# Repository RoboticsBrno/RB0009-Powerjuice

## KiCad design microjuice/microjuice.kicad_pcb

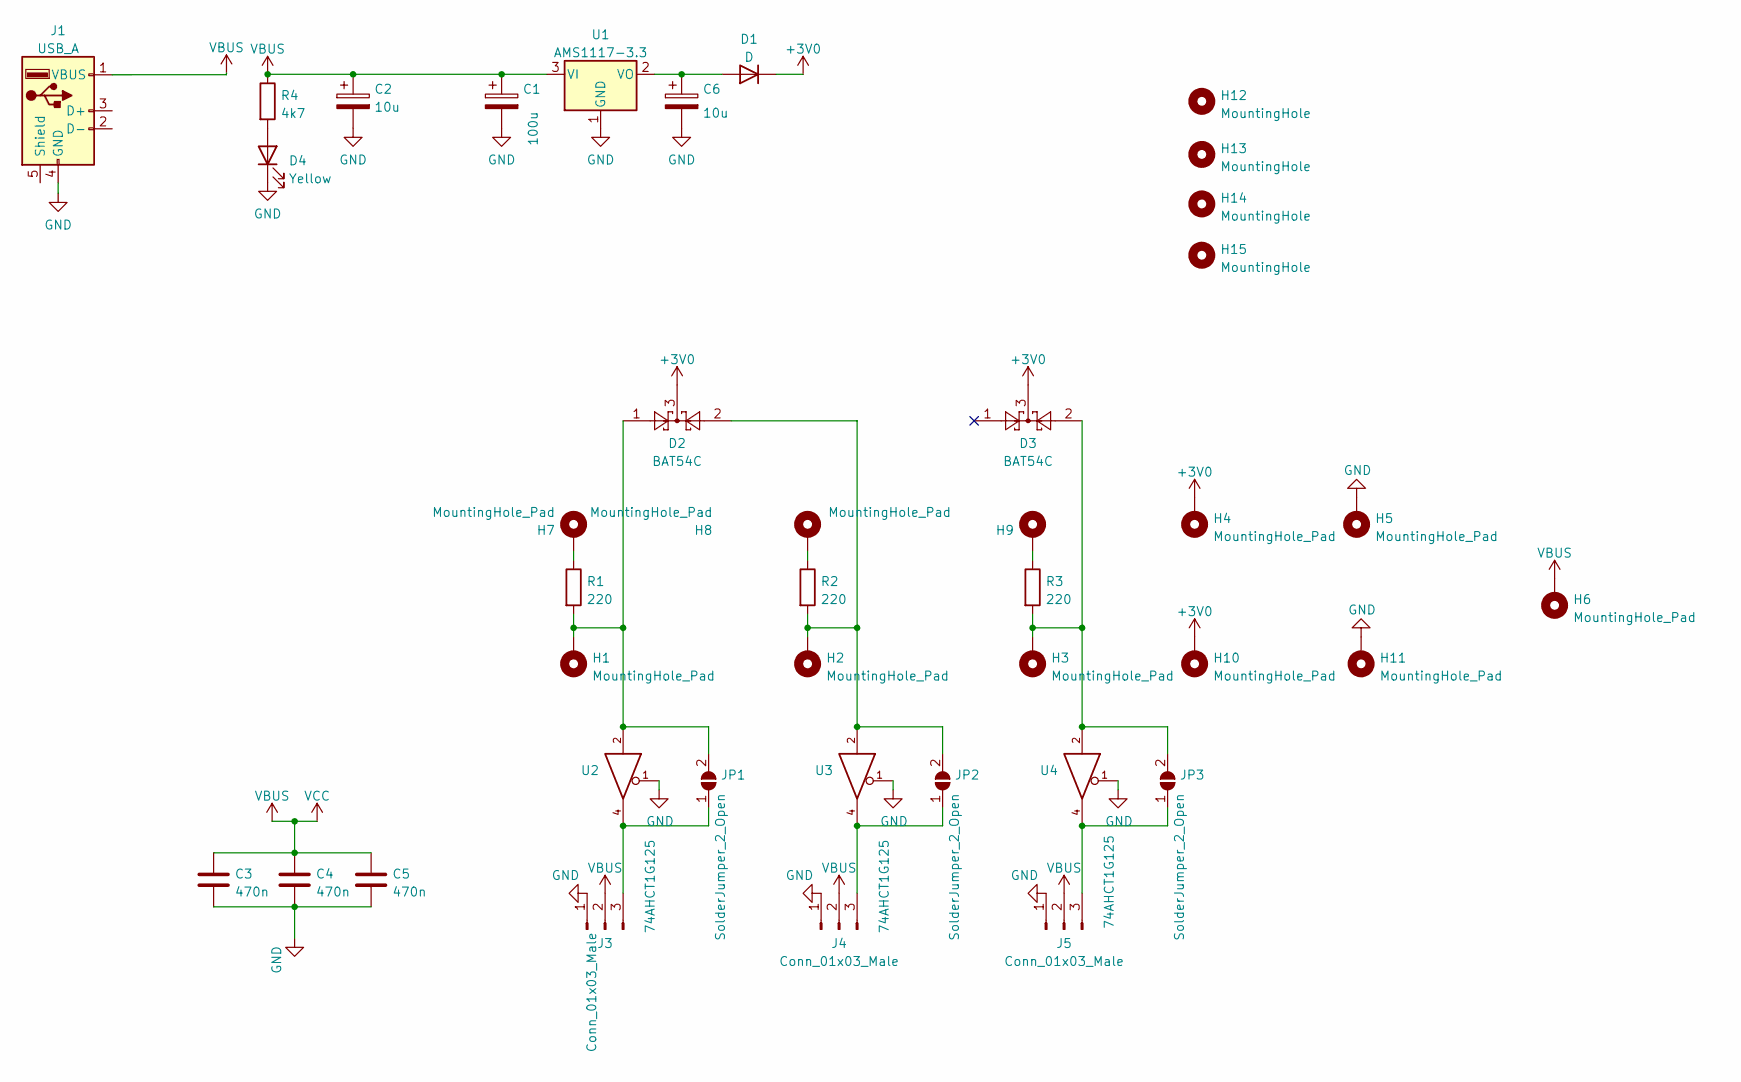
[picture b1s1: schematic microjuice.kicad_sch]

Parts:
C1: 100u; CP_Elec_6.3x5.4_Nichicon; LCSC C111600
C2, C6: 10u; CP_EIA-3216-18_Kemet-A; LCSC C7171
C3, C4, C5: 470n; C_0603_1608Metric; LCSC C1623
D1: D; D_SMA; LCSC C35722
D2, D3: BAT54C; SOT-23; LCSC C37704
D4: Yellow; LED_0603_1608Metric; LCSC C72038
H1, H2, H3, H6, H10, H11: MountingHole_Pad; SpuntDira
H4, H5, H7, H8, H9: MountingHole_Pad; SMTSO30; LCSC C2916371
H12, H13, H14, H15: MountingHole; MountingHole_3.2mm_M3
J1: USB_A; usb-PCB
J3, J4, J5: Conn_01x03_Male; PinHeader_1x03_P2.54mm_Vertical
JP1, JP2, JP3: SolderJumper_2_Open; SolderJumper-2_P1.3mm_Open_TrianglePad1.0x1.5mm
R1, R2, R3: 220; R_0603_1608Metric; LCSC C22962
R4: 4k7; R_0603_1608Metric; LCSC C23162
U1: AMS1117-3.3; SOT-223-3_TabPin2; LCSC C6186
U2, U3, U4: 74AHCT1G125; SOT-23-5; LCSC C7484

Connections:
+3V0: D1.1 (K), D2.3, D3.3, H4.1, H10.1
GND: C1.2, C2.2, C3.1, C4.1, C5.1, C6.2, D4.1 (K), H5.1, H11.1, J1.4 (GND), J3.1, J4.1, J5.1, U1.1 (GND), U2.1, U2.3 (GND), U3.1, U3.3 (GND), U4.1, U4.3 (GND)
unnamed: C6.1, D1.2 (A), U1.2 (VO)
unnamed: D2.1, H1.1, JP1.2 (B), R1.2, U2.2
unnamed: D2.2, H2.1, JP2.2 (B), R2.2, U3.2
unnamed: D3.2, H3.1, JP3.2 (B), R3.2, U4.2
unnamed: D4.2 (A), R4.2
unnamed: H7.1, R1.1
unnamed: H8.1, R2.1
unnamed: H9.1, R3.1
unnamed: J3.3, JP1.1 (A), U2.4
unnamed: J4.3, JP2.1 (A), U3.4
unnamed: J5.3, JP3.1 (A), U4.4
VBUS: C1.1, C2.1, C3.2, C4.2, C5.2, H6.1, J1.1 (VBUS), J3.2, J4.2, J5.2, R4.1, U1.3 (VI), U2.5 (VCC), U3.5 (VCC), U4.5 (VCC)

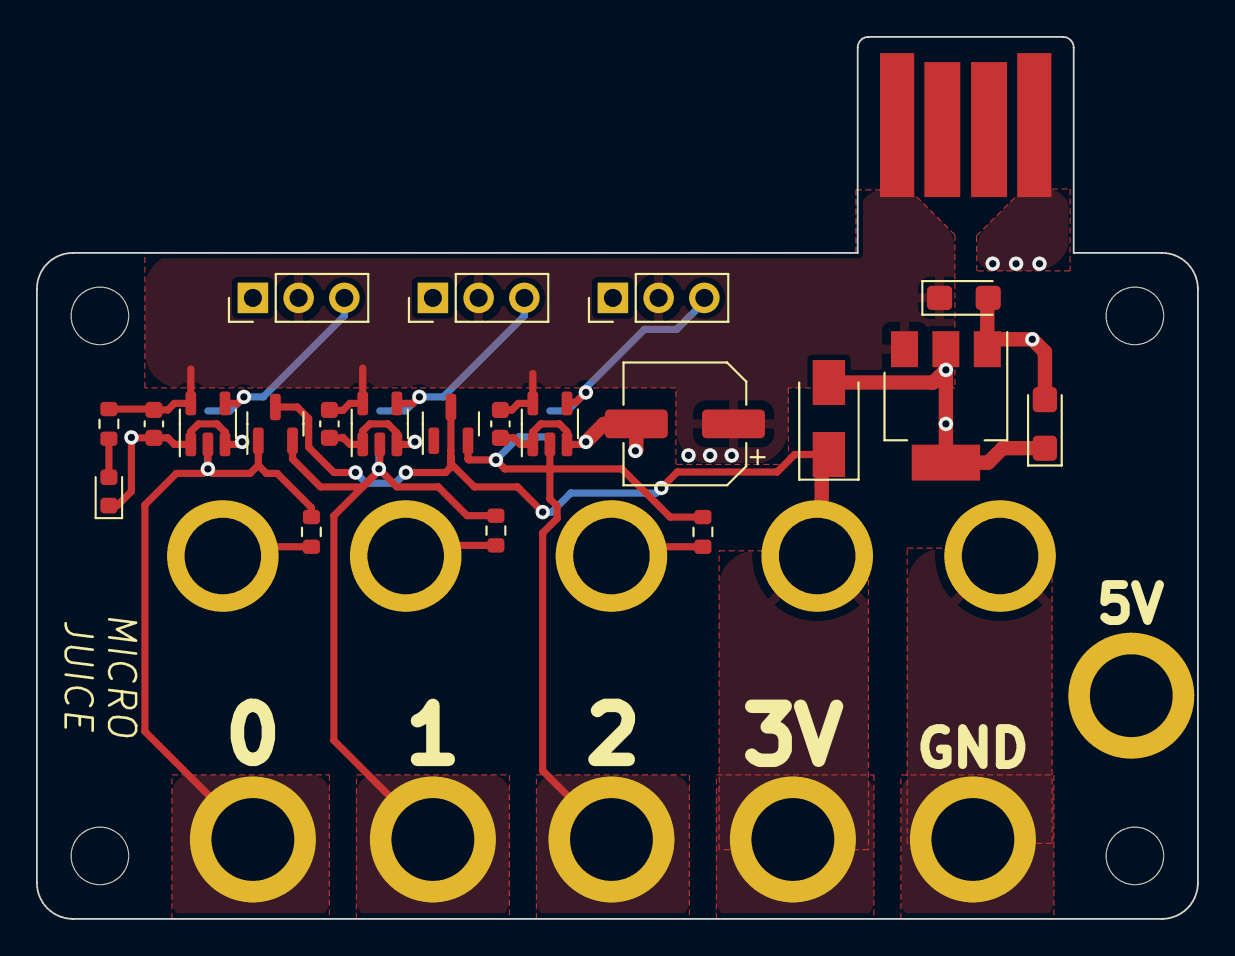
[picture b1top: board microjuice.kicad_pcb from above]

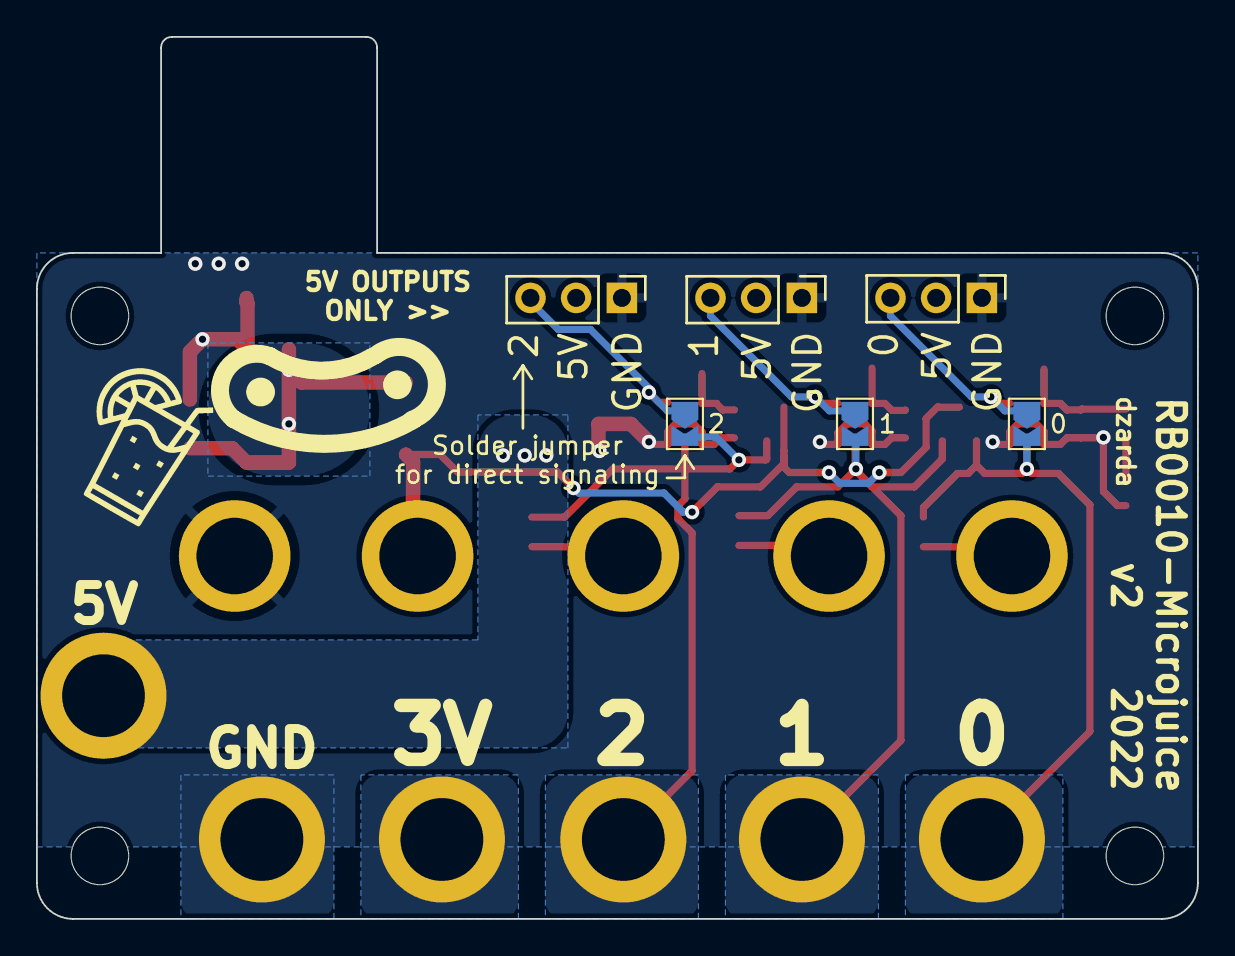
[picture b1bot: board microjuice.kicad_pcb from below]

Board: 2 copper layers, 64.5 x 49.0 mm, 41 parts (4 on the bottom side), 14 nets.

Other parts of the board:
Gw: LOGO

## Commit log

2022-06-01 Add v0
2023-07-28 Add v2
2023-07-28 Add v2 manufacturing data
